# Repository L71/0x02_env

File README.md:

0x02_env
========

Eurorack AD/ASR envelope and CV generator

This module generates a bipolar control voltage in response to a gate/trigger pulse.
The button selects how it responds to an input pulse: Attack-Decay or Attack-Sustain-Release. 
The zero and triggered (peak) levels are separately set anywhere within the output voltage range (-5 - +5 V).

** Work in progress **

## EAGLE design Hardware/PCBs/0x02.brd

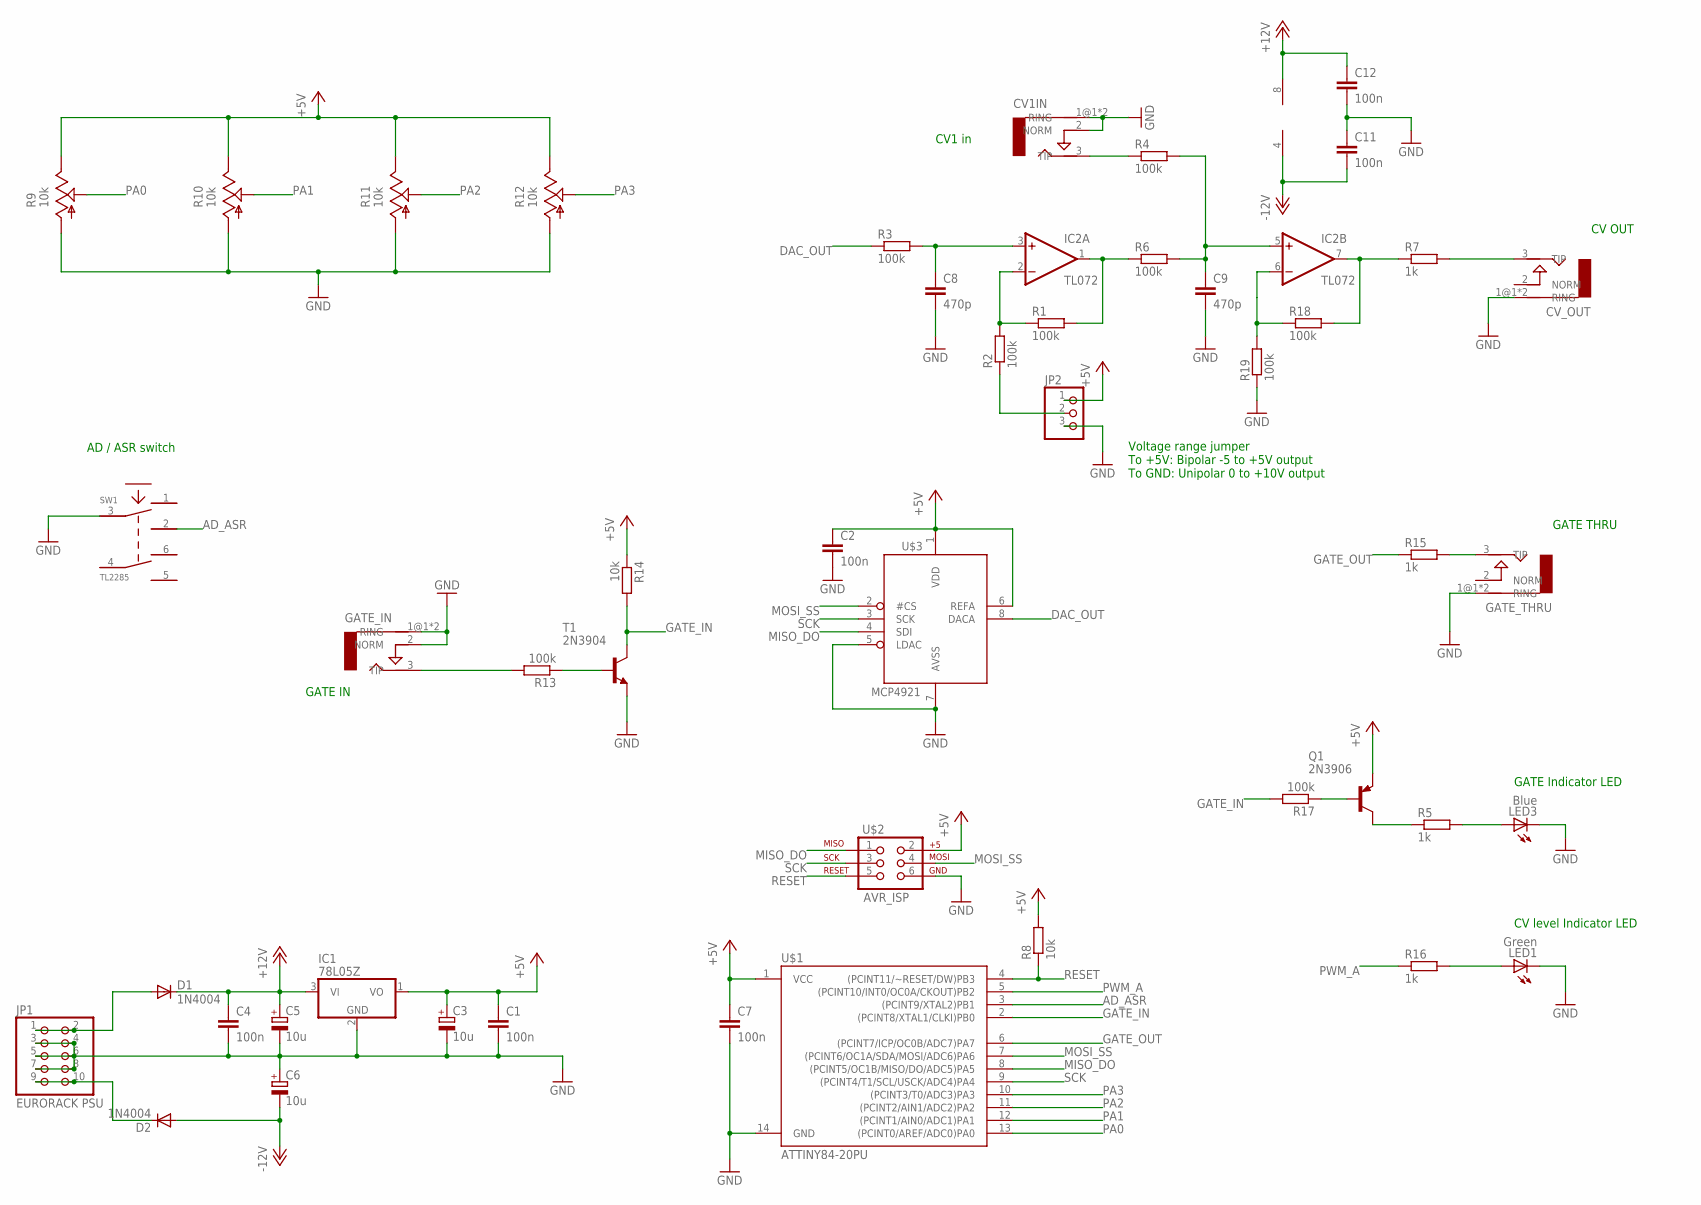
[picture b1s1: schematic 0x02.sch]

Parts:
C1, C2, C4, C7, C11, C12: 100n; C025-025X050
C3, C5, C6: 10u; E2,5-5
C8, C9: 470p; C025-025X050
CV1IN: AUDIO-JACKERTHENVAR; ERTHENVAR-JACK
CV_OUT: CV_OUT; ERTHENVAR-JACK
D1, D2: 1N4004; DO41-10
GATE_IN: AUDIO-JACKERTHENVAR; ERTHENVAR-JACK
GATE_THRU: CV_OUT; ERTHENVAR-JACK
IC1: 78L05Z; TO92
IC2: TL072; DIL08
JP1: EURORACK PSU; 2X05
JP2: PINHD-1X3; 1X03
LED1: Green; LED5MM
LED3: Blue; LED5MM
Q1: 2N3906; TO92
R1, R2, R3, R4, R6, R13, R17, R18, R19: 100k; 0207/2V
R5, R7, R15, R16: 1k; 0207/2V
R8, R14: 10k; 0207/2V
R9, R10, R11, R12: 10k; ALPS_POT_VERTICAL
SW1: TL2285; TL2285_PCB
T1: 2N3904; TO92
U$1: ATTINY84-20PU; DIL14
U$2: AVR_ISP; 2X3
U$3: MCP4921; DIL08

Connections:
+5V: C1.1, C2.1, C3.+, C7.1, IC1.1 (VO), JP2.1, Q1.3 (E), R8.2, R9.P$1 (E), R10.P$1 (E), R11.P$1 (E), R12.P$1 (E), R14.1, U$1.1 (VCC), U$2.2, U$3.1 (VDD), U$3.6 (REFA)
+12V: C4.1, C5.+, C12.1, D1.C, IC1.3 (VI), IC2.8 (V+)
+12V_IN: D1.A, JP1.1, JP1.2
-12V: C6.-, C11.2, D2.A, IC2.4 (V-)
-12V_IN: D2.C, JP1.9, JP1.10
AD_ASR: SW1.2, U$1.3 ((PCINT9/XTAL2)PB1)
DAC_OUT: R3.1, U$3.8 (DACA)
GATE_IN: R14.2, R17.2, T1.1 (C), U$1.2 ((PCINT8/XTAL1/CLKI)PB0)
GATE_OUT: R15.1, U$1.6 ((PCINT7/ICP/OC0B/ADC7)PA7)
GND: C1.2, C2.2, C3.-, C4.2, C5.-, C6.+, C7.2, C8.2, C9.2, C11.1, C12.2, CV1IN.1@1 (RING), CV1IN.1@2 (RING), CV1IN.2 (NORM), CV_OUT.1@1 (RING), CV_OUT.1@2 (RING), GATE_IN.1@1 (RING), GATE_IN.1@2 (RING), GATE_IN.2 (NORM), GATE_THRU.1@1 (RING), GATE_THRU.1@2 (RING), IC1.2 (GND), JP1.3, JP1.4, JP1.5, JP1.6, JP1.7, JP1.8, JP2.3, LED1.K (C), LED3.K (C), R9.P$3 (A), R10.P$3 (A), R11.P$3 (A), R12.P$3 (A), R19.1, SW1.3, T1.3 (E), U$1.14 (GND), U$2.6, U$3.5 (LDAC), U$3.7 (AVSS)
MISO_DO: U$1.8 ((PCINT5/OC1B/MISO/DO/ADC5)PA5), U$2.1, U$3.4 (SDI)
MOSI_SS: U$1.7 ((PCINT6/OC1A/SDA/MOSI/ADC6)PA6), U$2.4, U$3.2 (#CS)
unnamed: R13.1, T1.2 (B)
unnamed: Q1.1 (C), R5.1
unnamed: LED3.A, R5.2
unnamed: Q1.2 (B), R17.1
unnamed: C8.1, IC2.3 (+IN), R3.2
unnamed: JP2.2, R2.1
unnamed: GATE_THRU.3 (TIP), R15.2
unnamed: GATE_IN.3 (TIP), R13.2
unnamed: IC2.2 (-IN), R1.1, R2.2
unnamed: IC2.1 (OUT), R1.2, R6.1
unnamed: CV_OUT.3 (TIP), R7.2
unnamed: C9.1, IC2.5 (+IN), R4.2, R6.2
unnamed: IC2.6 (-IN), R18.1, R19.2
unnamed: CV1IN.3 (TIP), R4.1
unnamed: IC2.7 (OUT), R7.1, R18.2
unnamed: LED1.A, R16.2
PA0: R9.P$2 (S), U$1.13 ((PCINT0/AREF/ADC0)PA0)
PA1: R10.P$2 (S), U$1.12 ((PCINT1/AIN0/ADC1)PA1)
PA2: R11.P$2 (S), U$1.11 ((PCINT2/AIN1/ADC2)PA2)
PA3: R12.P$2 (S), U$1.10 ((PCINT3/T0/ADC3)PA3)
PWM_A: R16.1, U$1.5 ((PCINT10/INT0/OC0A/CKOUT)PB2)
RESET: R8.1, U$1.4 ((PCINT11/~RESET/DW)PB3), U$2.5
SCK: U$1.9 ((PCINT4/T1/SCL/USCK/ADC4)PA4), U$2.3, U$3.3 (SCK)

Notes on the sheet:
CV OUT
GATE THRU
GATE IN
CV1 in
AD / ASR switch
CV level Indicator LED
GATE Indicator LED
Voltage range jumper To +5V: Bipolar -5 to +5V output To GND: Unipolar 0 to +10V output

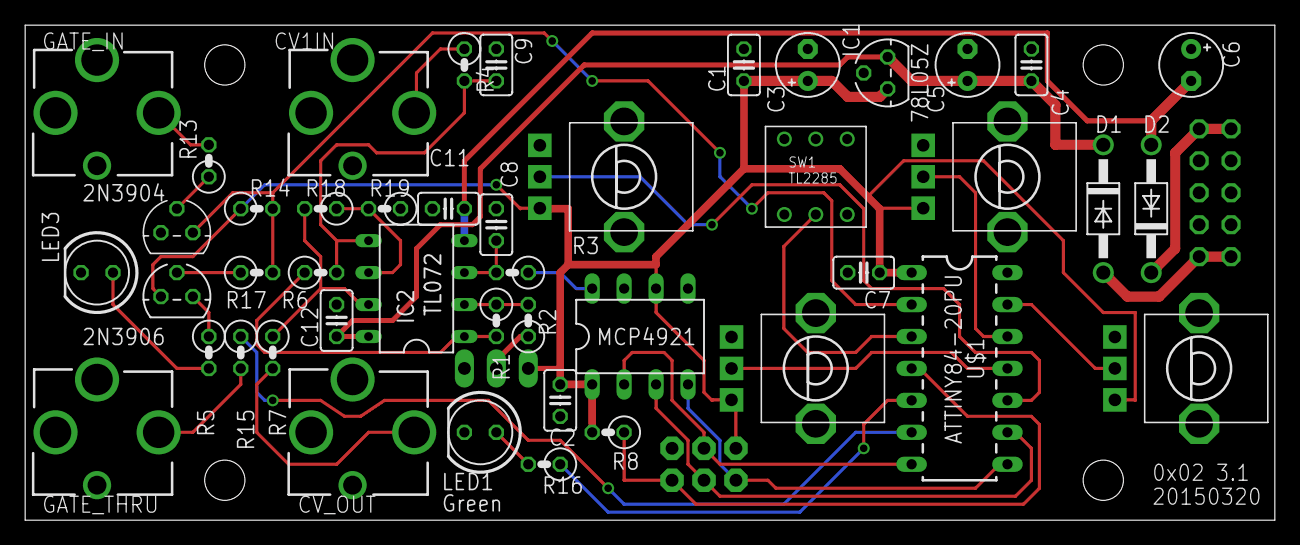
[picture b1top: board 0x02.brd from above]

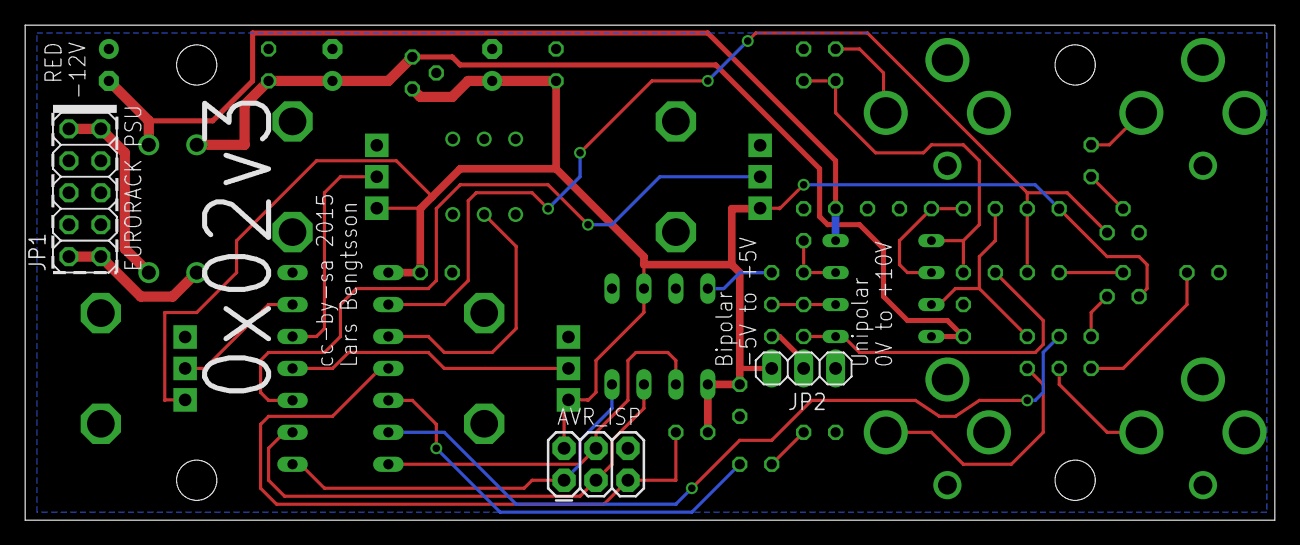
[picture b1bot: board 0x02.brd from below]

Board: 2 copper layers, 99.4 x 39.4 mm, 48 parts (3 on the bottom side), 35 nets.

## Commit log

2014-12-07 Initial upload of final code.
2014-12-07 Added PCBEagle files + Panels.
2014-12-07 Added panel files (for real! :) )
2014-12-07 Added BOM spreadsheet.
2015-02-01 Don't track Eagle backup files
2015-03-11 Checkin of code & PCB for version 3 with DAC instead of PWM output.
2015-03-20 Added jumper to set voltage output range, -5V to +5V or 0-+10V.
2015-05-10 Make voltage mixer into a true voltage adder (ext cv in tied to GND when unused, and 2x gain in output amp).

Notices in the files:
Hardware/PCBs/0x02.brd:
cc-by-sa 2015
parts and their libraries:
SparkFun-DigitalIC: Licensing: Creative Commons ShareAlike 4.0 International - https://creativecommons.org/licenses/by-sa/4.0
